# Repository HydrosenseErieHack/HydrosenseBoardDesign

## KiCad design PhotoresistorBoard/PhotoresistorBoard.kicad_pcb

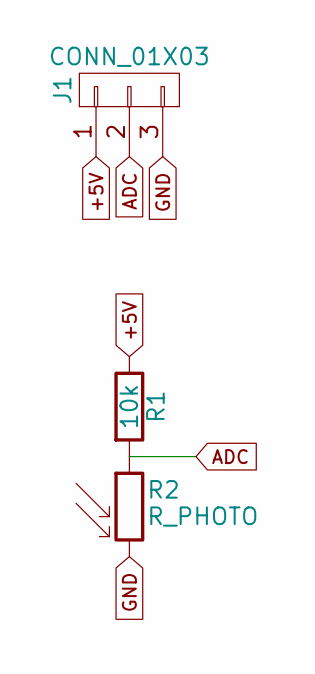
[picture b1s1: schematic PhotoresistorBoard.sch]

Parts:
J1: CONN_01X03; Pin_Header_Angled_1x03_Pitch2.54mm
R1: 10k; R_0603
R2: R_PHOTO; Resistor_LDR_4.9x4.2_RM2.54

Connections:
+5V: J1.1, R1.1
ADC: J1.2, R1.2, R2.1
GND: J1.3, R2.2

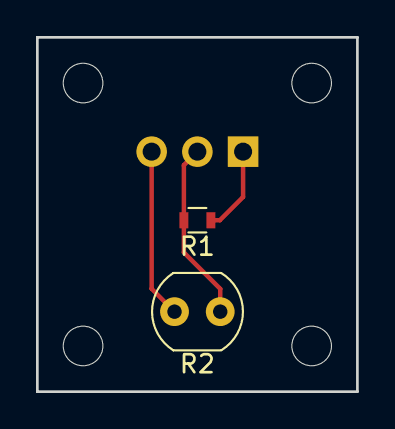
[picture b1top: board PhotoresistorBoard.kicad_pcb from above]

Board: 2 copper layers, 17.8 x 19.7 mm, 3 parts (1 on the bottom side), 3 nets.

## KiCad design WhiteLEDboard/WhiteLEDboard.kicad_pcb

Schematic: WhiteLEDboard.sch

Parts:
D1: LED; LED_D5.0mm
J1: CONN_01X02; Pin_Header_Angled_1x02_Pitch2.54mm
R1: 10k; R_0603_HandSoldering

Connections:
+5V: J1.1, R1.1
GND: D1.1 (K), J1.2
unnamed: D1.2 (A), R1.2

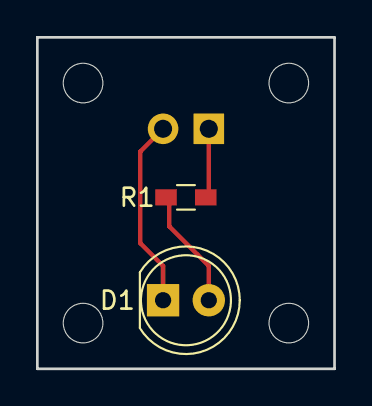
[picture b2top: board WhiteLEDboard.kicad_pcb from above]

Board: 2 copper layers, 16.5 x 18.4 mm, 3 parts (1 on the bottom side), 3 nets.

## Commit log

2017-04-22 Added KiCad files
2017-04-23 Updates to board (added text cause we fancy)
2017-04-23 Added photoresistor board
2017-04-23 Added WhiteLEDboard
